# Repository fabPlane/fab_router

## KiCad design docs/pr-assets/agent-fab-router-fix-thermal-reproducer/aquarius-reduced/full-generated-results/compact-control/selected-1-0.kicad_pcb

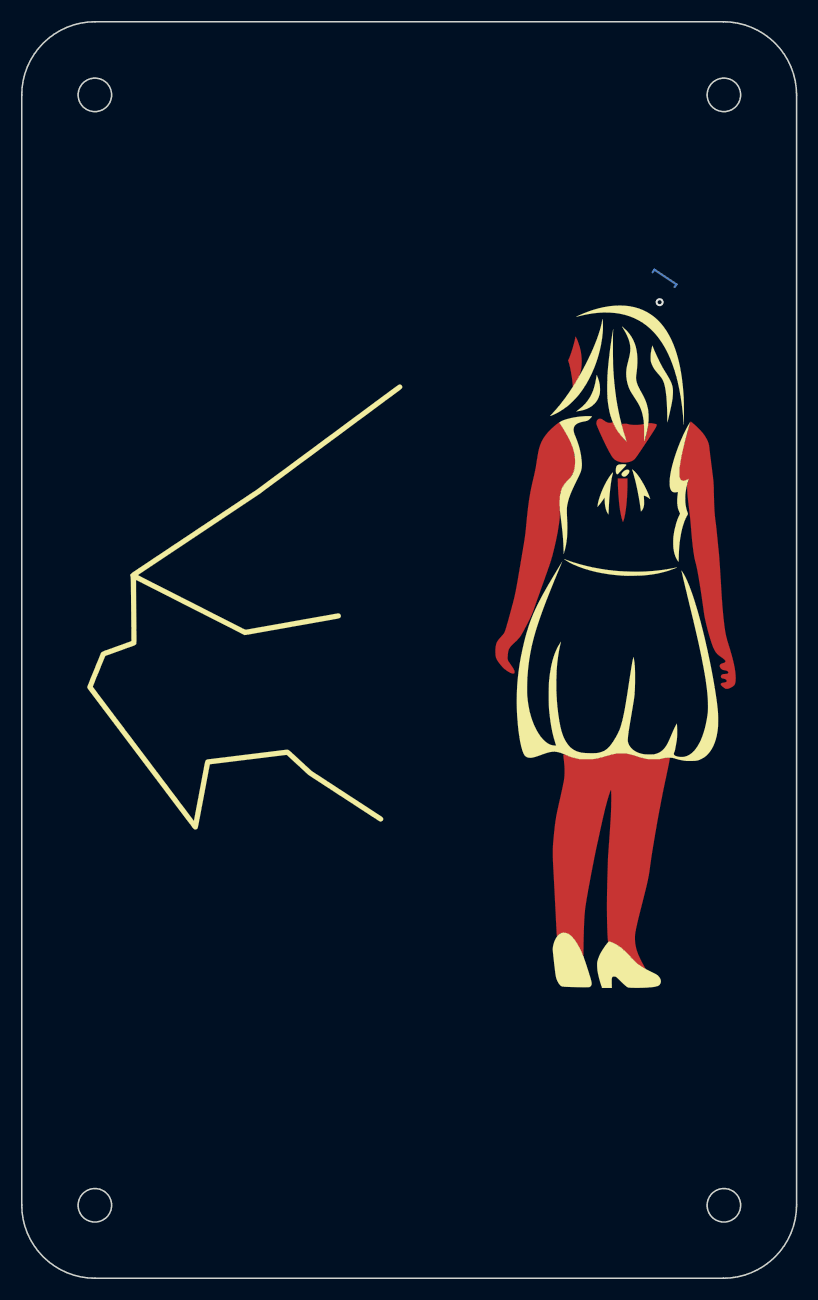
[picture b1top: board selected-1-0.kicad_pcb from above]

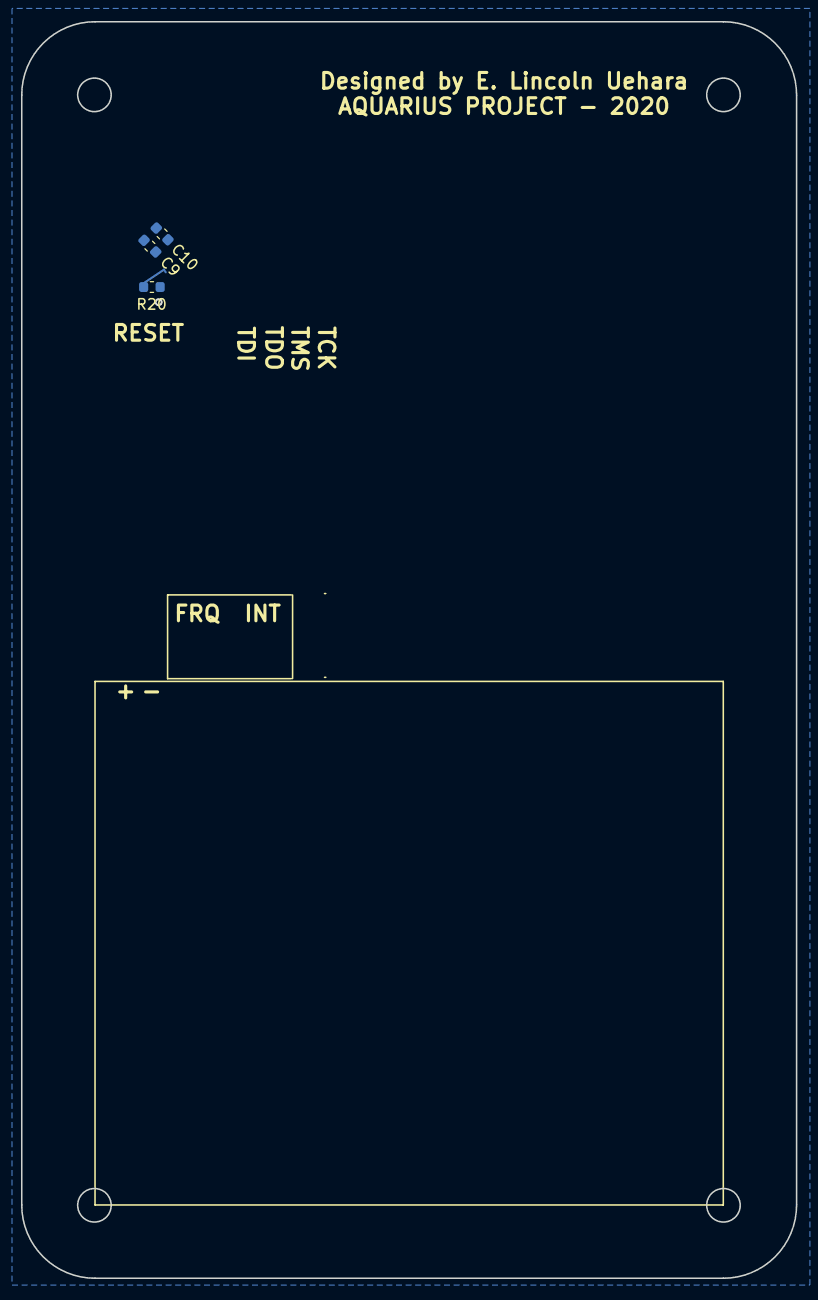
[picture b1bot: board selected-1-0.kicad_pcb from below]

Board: 2 copper layers, 74.0 x 120.0 mm, 4 parts (3 on the bottom side), 2 nets.

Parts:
C9: 0.01uF; C_0603_1608Metric
C10: 0.1uF; C_0603_1608Metric
R20: 0; R_0603_1608Metric
X1: theGirl

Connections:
+3V3: C9.1, C10.1
GNDD: C9.2, C10.2, R20.1

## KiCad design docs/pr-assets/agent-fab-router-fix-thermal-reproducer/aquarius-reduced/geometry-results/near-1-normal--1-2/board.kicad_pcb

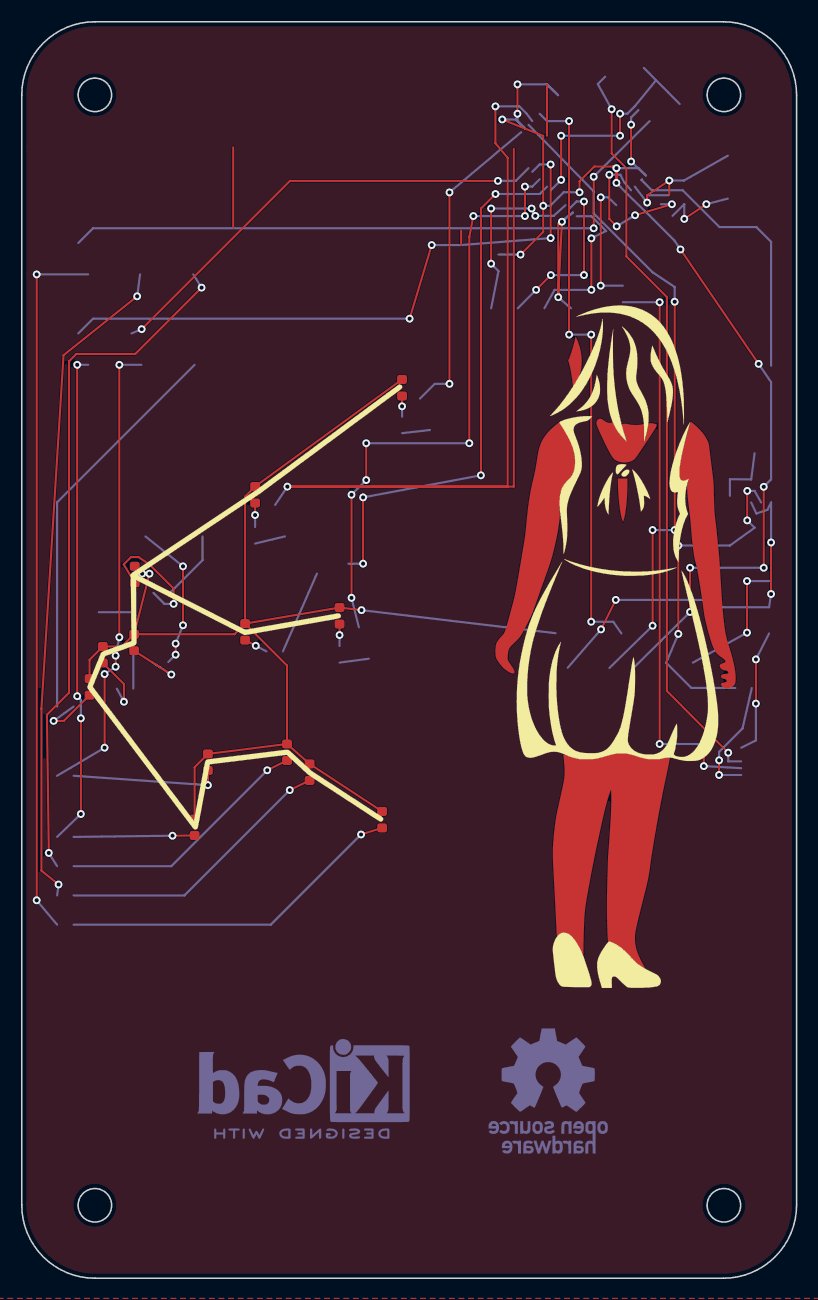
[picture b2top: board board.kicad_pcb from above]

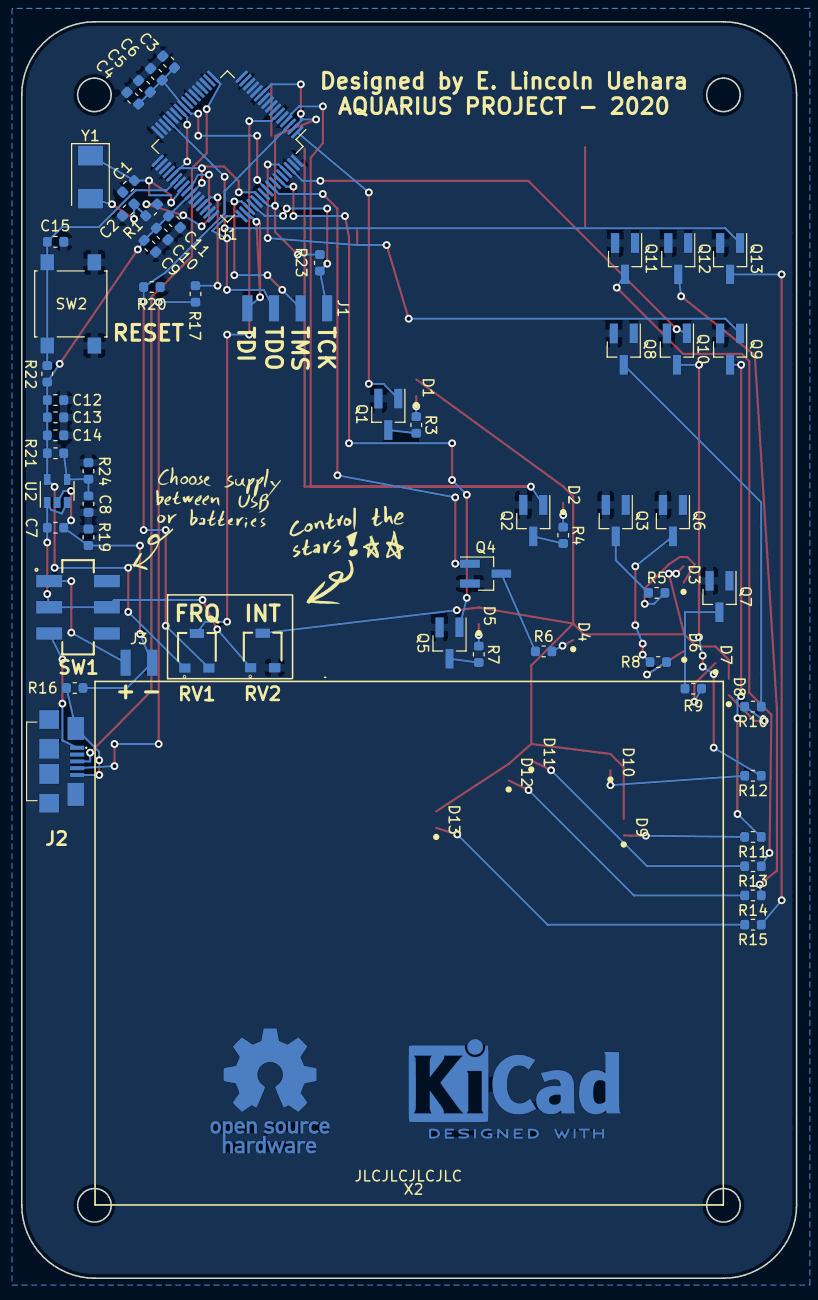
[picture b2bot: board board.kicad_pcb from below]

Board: 2 copper layers, 74.0 x 120.0 mm, 79 parts (64 on the bottom side), 63 nets.

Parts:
C1, C2: 10pF; C_0603_1608Metric
C3: 2.2uF; C_0603_1608Metric
C4, C7, C14: 1.0uF; C_0603_1608Metric
C5, C6, C10, C12, C15: 0.1uF; C_0603_1608Metric
C8, C9, C11, C13: 0.01uF; C_0603_1608Metric
D1, D2, D3, D4, D5, D6, D7, D8, D9, D10, D11, D12, D13: LED; LED_STAR_0603
J1: Conn_01x04; PinHeader_1x04_P2.54mm_SMD
J2: USB_B_Micro; ZX62B5PA33
J3: Conn_01x02; PinHeader_1x02_P2.54mm_SMD
Q1, Q2, Q3, Q4, Q5, Q6, Q7, Q8, Q9, Q10, Q11, Q12, Q13: DTC114E; SOT-23_Handsoldering
R1, R16, R17, R19, R20: 0; R_0603_1608Metric
R3, R4, R5, R6, R7, R8, R9, R10, R11, R12, R13, R14, R15: R100; R_0603_1608Metric
R21: 51k; R_0603_1608Metric
R22: 10k; R_0603_1608Metric
R23: 100k; R_0603_1608Metric
R24: 30k; R_0603_1608Metric
RV1, RV2: R_POT; PVG3A
SW1: SW_DPDT_x2; JS202011SCQN
SW2: SW_Push; SW_SPST_B3S-1000
U1: TM4C1231C3PM; LQFP-64_10x10mm_P0.5mm
U2: TPS73633DBV; SOT-23-5
X1: theGirl
X2: jlcpcb_order
X3: DesignedWithKicad; KiCad-Logo2_8mm_Copper
X4: OpenSourceHardware; OSHW-Logo_11.4x12mm_Copper
X5: choose_indication
X6: control_indication
Y1: 16MHz; Crystal_SMD_Abracon_ABM3-2Pin_5.0x3.2mm

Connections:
+3V3: C9.1, C10.1, C11.1, C12.1, C13.1, C14.1, R21.1, R22.1, R23.2, RV1.1, U1.2, U1.11, U1.26, U1.37, U1.42, U1.54, U2.5
/Inputs/D+: J2.3, U1.17
/Inputs/D-: J2.2, U1.18
/Inputs/LED_PWR: D1.2, D2.2, D3.2, D4.2, D5.2, D6.2, D7.2, D8.2, D9.2, D10.2, D11.2, D12.2, D13.2, RV2.2
/Inputs/PB0: R17.2, U1.45
/Inputs/POT00: RV1.2, U1.6
/Inputs/RST: C15.1, R22.2, SW2.2, U1.38
/Inputs/TCK: J1.1, R23.1, U1.52
/Inputs/TDI: J1.4, U1.50
/Inputs/TDO: J1.3, U1.49
/Inputs/TMS: J1.2, U1.51
/Inputs/USB_PWR: J2.1, SW1.3
/Leds/Stars/LED0: Q1.1, U1.1
/Leds/Stars/LED1: Q2.1, U1.4
/Leds/Stars/LED2: Q3.1, U1.58
/Leds/Stars/LED3: Q4.1, U1.57
/Leds/Stars/LED4: Q5.1, U1.59
/Leds/Stars/LED5: Q6.1, U1.60
/Leds/Stars/LED6: Q7.1, U1.16
/Leds/Stars/LED7: Q8.1, U1.15
/Leds/Stars/LED8: Q9.1, U1.61
/Leds/Stars/LED9: Q10.1, U1.62
/Leds/Stars/LED10: Q11.1, U1.23
/Leds/Stars/LED11: Q12.1, U1.24
/Leds/Stars/LED12: Q13.1, U1.29
GNDA: R20.2, RV1.3, U1.3
GNDD: C1.2, C2.2, C3.2, C4.2, C5.2, C6.2, C8.2, C9.2, C10.2, C11.2, C12.2, C13.2, C14.2, C15.2, Q1.2, Q2.2, Q3.2, Q4.2, Q5.2, Q6.2, Q7.2, Q8.2, Q9.2, Q10.2, Q11.2, Q12.2, Q13.2, R19.2, R20.1, R24.2, RV2.3, SW2.1, U1.5, U1.7, U1.8, U1.9, U1.10, U1.12, U1.13, U1.14, U1.19, U1.20, U1.21, U1.22, U1.27, U1.28, U1.30, U1.31, U1.32, U1.34, U1.35, U1.39, U1.43, U1.44, U1.46, U1.47, U1.48, U1.53, U1.55, U1.63, U1.64
GNDPWR: C7.2, J3.2, R16.2, R19.1, U2.2
unnamed: C1.1, U1.40, Y1.1
unnamed: C2.1, R1.2, Y1.2
unnamed: C3.1, C4.1, C5.1, C6.1, U1.25, U1.56
unnamed: C8.1, R21.2, R24.1, U2.4
unnamed: D1.1, R3.2
unnamed: D2.1, R4.2
unnamed: D3.1, R5.2
unnamed: D4.1, R6.2
unnamed: D5.1, R7.2
unnamed: D6.1, R8.2
unnamed: D7.1, R9.2
unnamed: D8.1, R10.2
unnamed: D9.1, R11.2
unnamed: D10.1, R12.2
unnamed: D11.1, R13.2
unnamed: D12.1, R14.2
unnamed: D13.1, R15.2
unnamed: J2.4, R17.1
unnamed: J2.5, J2.6, R16.1
unnamed: J3.1, SW1.1
unnamed: Q1.3, R3.1
unnamed: Q2.3, R4.1
unnamed: Q3.3, R5.1
unnamed: Q4.3, R6.1
unnamed: Q5.3, R7.1
unnamed: Q6.3, R8.1
unnamed: Q7.3, R9.1
unnamed: Q8.3, R10.1
unnamed: Q9.3, R11.1
unnamed: Q10.3, R12.1
unnamed: Q11.3, R13.1
unnamed: Q12.3, R14.1
unnamed: Q13.3, R15.1
unnamed: R1.1, U1.41
VBUS: C7.1, RV2.1, SW1.2, SW1.5, U2.1, U2.3

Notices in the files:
docs/pr-assets/agent-fab-router-fix-thermal-reproducer/aquarius-reduced/geometry-results/near-1-normal--1-2/board.kicad_pcb:
creativecommons.org/licenses/by/4.0
License: CC BY 4.0
